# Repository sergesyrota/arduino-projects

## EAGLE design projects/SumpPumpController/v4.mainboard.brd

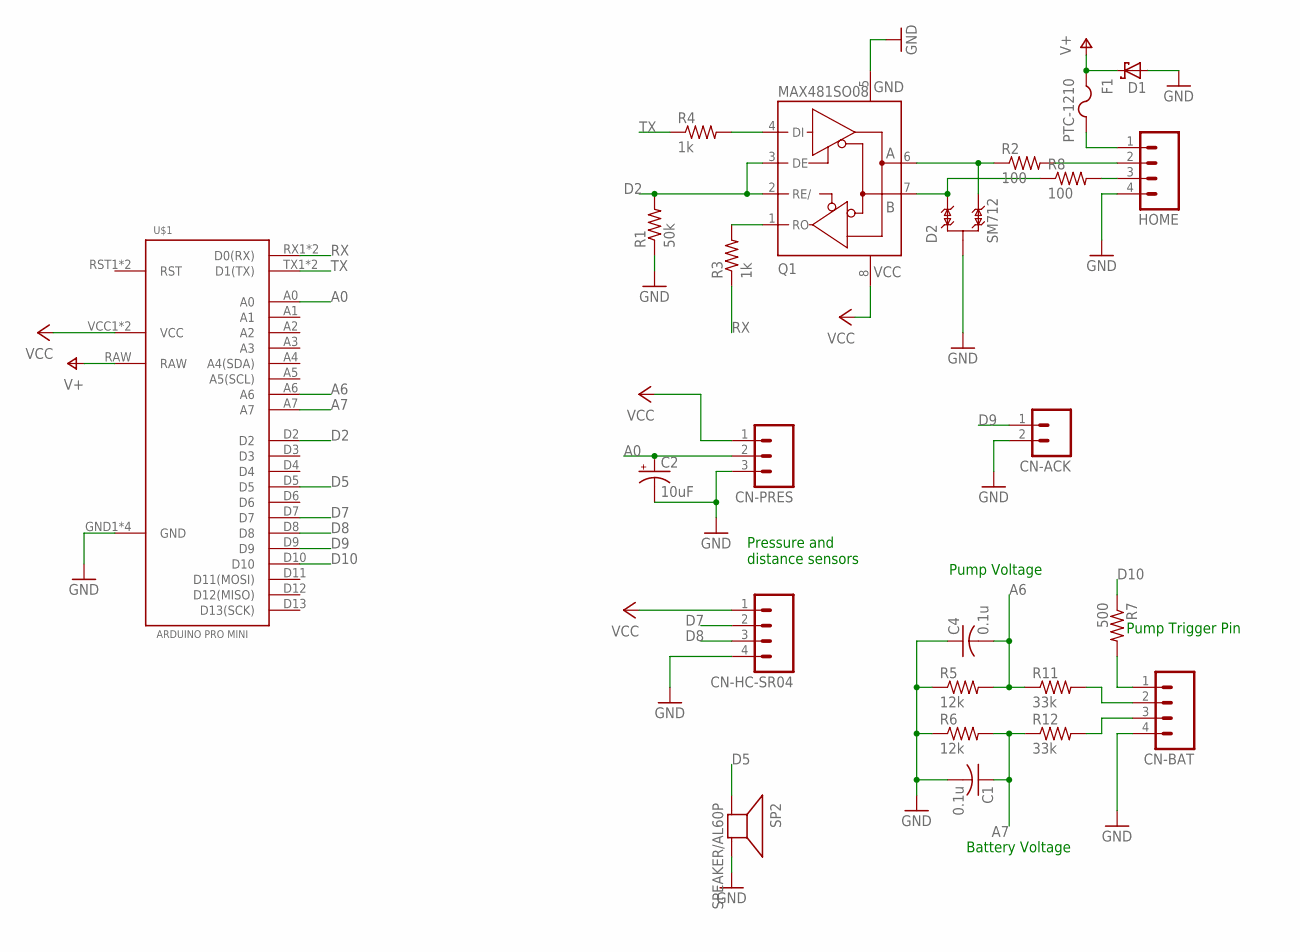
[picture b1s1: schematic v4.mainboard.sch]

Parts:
C1, C4: 0.1u; C0603K
C2: 10uF; E2-5
CN-ACK: M02; 02P
CN-BAT: M04; 04P
CN-HC-SR04: M04; 04P
CN-PRES: M03; 03P
D1: SCHOTTKY-DIODESMC; SMC
D2: SM712; SOT23-3
F1: PTC-1210; 1210
HOME: M04; 04P
Q1: MAX481SO08; SO08
R1: 50k; R0603
R2, R8: 100; R0603
R3, R4: 1k; R0603
R5, R6: 12k; R0603
R7: 500; R0603
R11, R12: 33k; R0603
SP2: SPEAKER/AL60P; AL60P
U$1: ARDUINO-PRO-MINI

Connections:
A0: C2.+, CN-PRES.2, U$1.A0
A6: C4.2, R5.2, R11.1, U$1.A6
A7: C1.1, R6.2, R12.1, U$1.A7
D2: Q1.2 (RE/), Q1.3 (DE), R1.2, U$1.D2
D5: SP2.1 (+), U$1.D5
D7: CN-HC-SR04.2, U$1.D7
D8: CN-HC-SR04.3, U$1.D8
D9: CN-ACK.1, U$1.D9
D10: R7.1, U$1.D10
GND: C1.2, C2.-, C4.1, CN-ACK.2, CN-BAT.4, CN-HC-SR04.4, CN-PRES.3, D1.A, D2.3, HOME.4, Q1.5 (GND), R1.1, R5.1, R6.1, SP2.2 (-), U$1.GND1 (GND), U$1.GND2 (GND), U$1.GND3 (GND), U$1.GND4 (GND)
unnamed: F1.2, HOME.1
unnamed: D2.2, Q1.7 (B), R8.1
unnamed: Q1.1 (RO), R3.2
unnamed: Q1.4 (DI), R4.2
unnamed: HOME.3, R8.2
unnamed: HOME.2, R2.2
unnamed: D2.1, Q1.6 (A), R2.1
unnamed: CN-BAT.2, R11.2
unnamed: CN-BAT.3, R12.2
unnamed: CN-BAT.1, R7.2
RX: R3.1, U$1.RX1 (D0(RX)), U$1.RX2 (D0(RX))
TX: R4.1, U$1.TX1 (D1(TX)), U$1.TX2 (D1(TX))
V+: D1.C, F1.1, U$1.RAW
VCC: CN-HC-SR04.1, CN-PRES.1, Q1.8 (+5V), U$1.VCC1 (VCC), U$1.VCC2 (VCC)

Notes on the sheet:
Battery Voltage
Pump Voltage
Pump Trigger Pin
Pressure and distance sensors

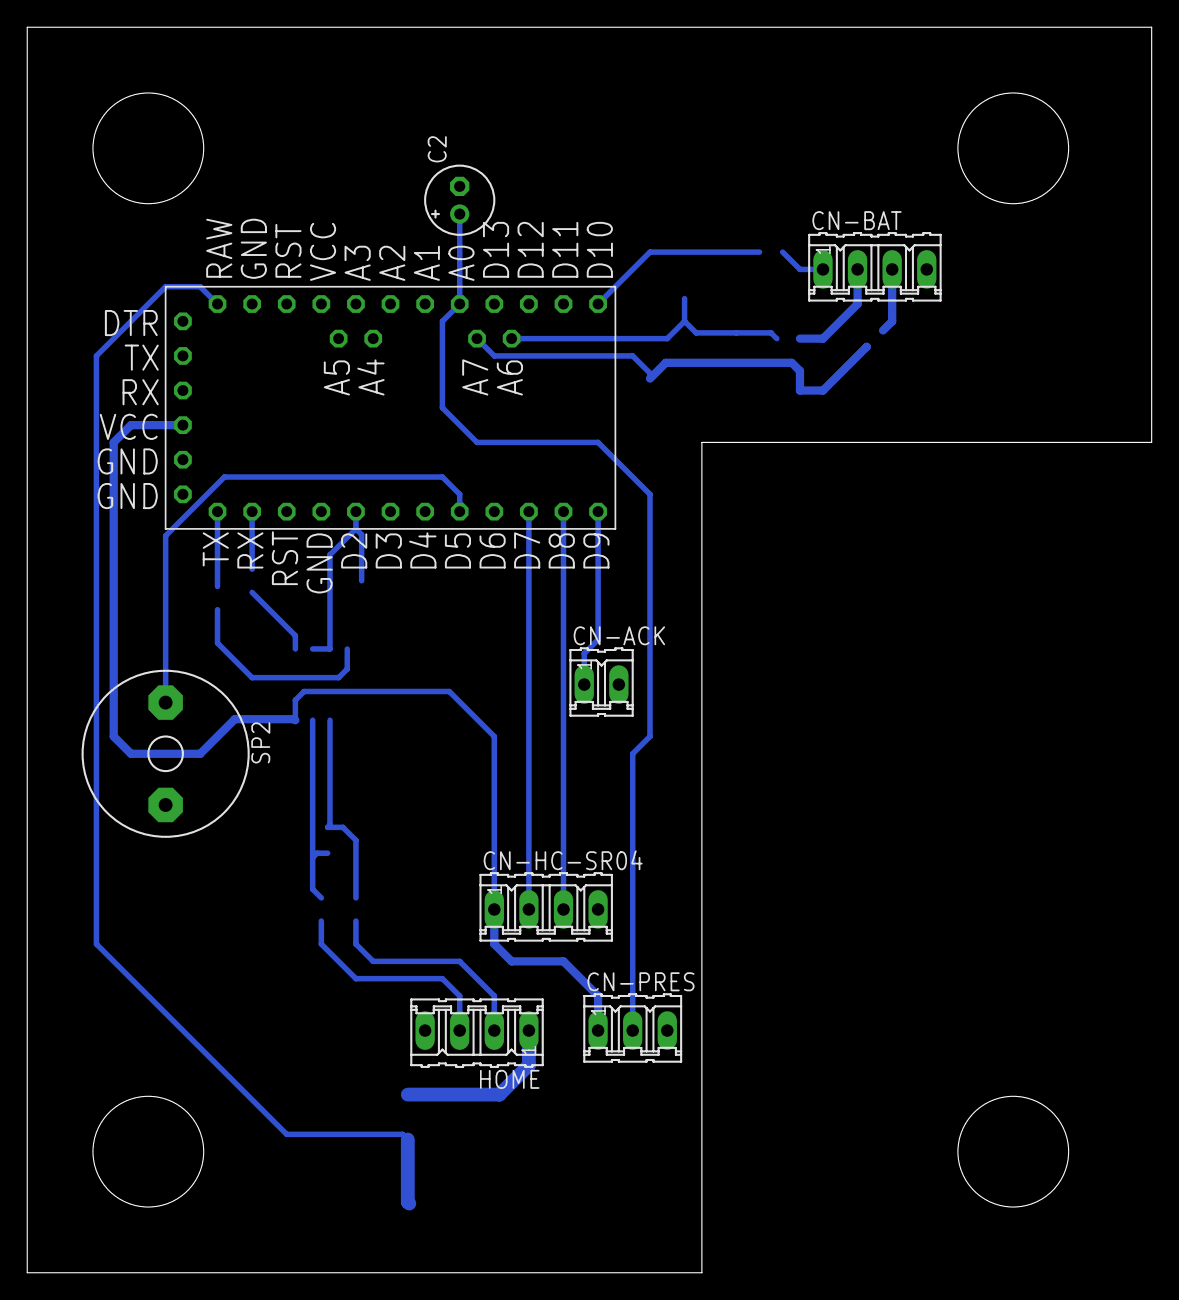
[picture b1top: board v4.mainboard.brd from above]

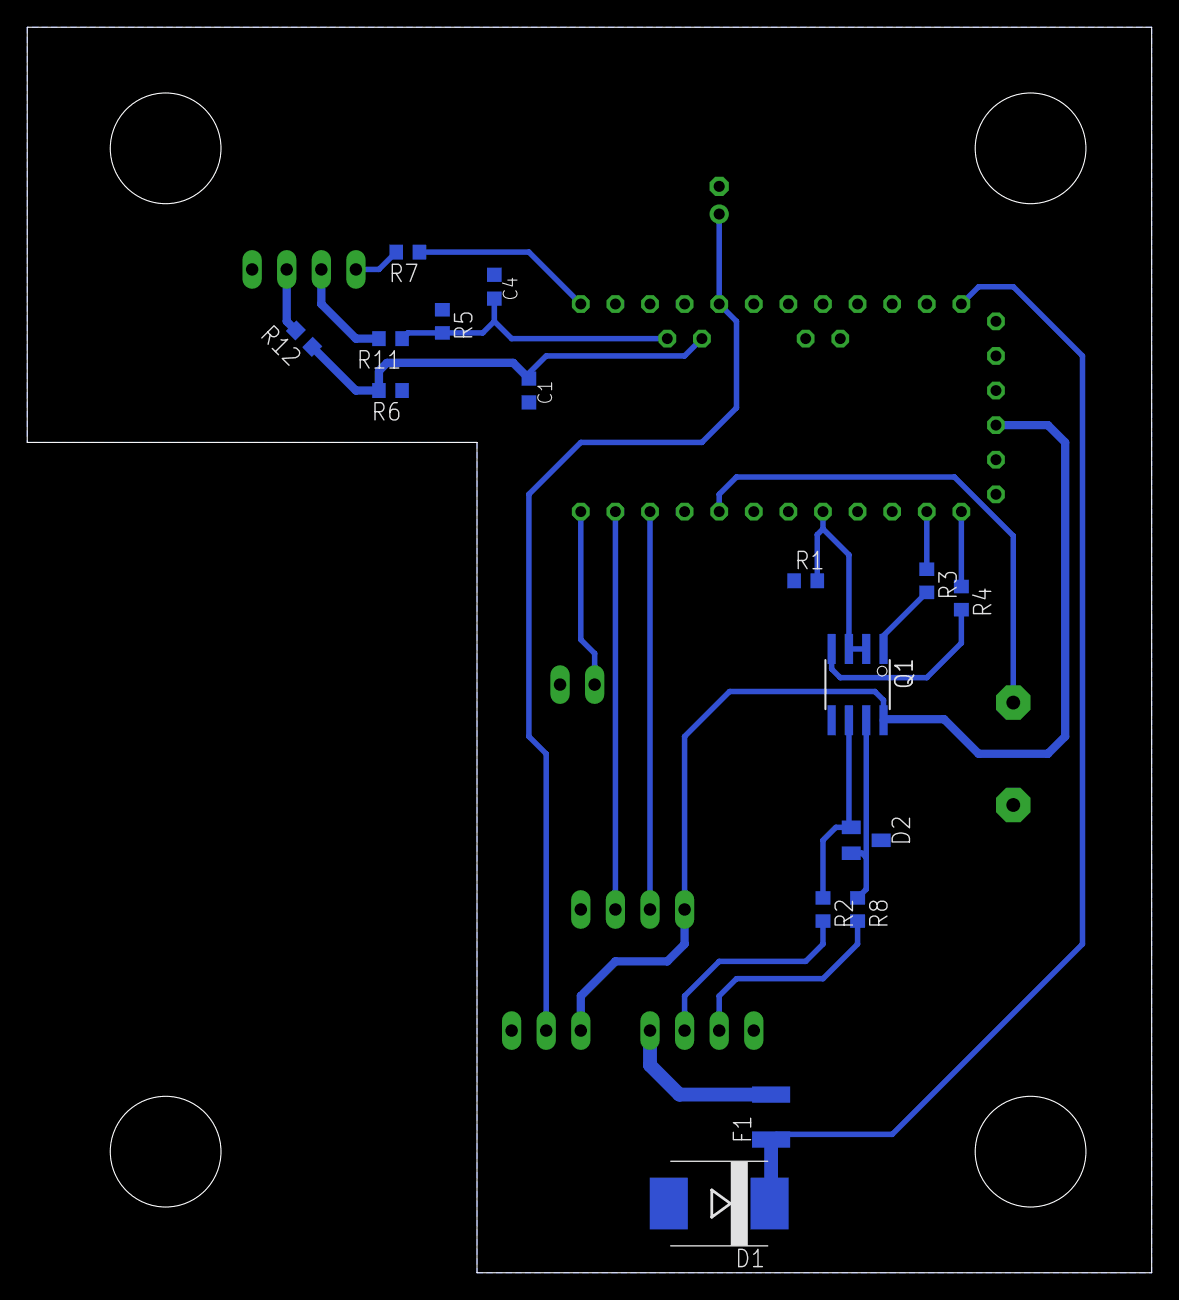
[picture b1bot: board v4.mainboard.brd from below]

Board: 2 copper layers, 82.5 x 91.4 mm, 24 parts (16 on the bottom side), 24 nets.

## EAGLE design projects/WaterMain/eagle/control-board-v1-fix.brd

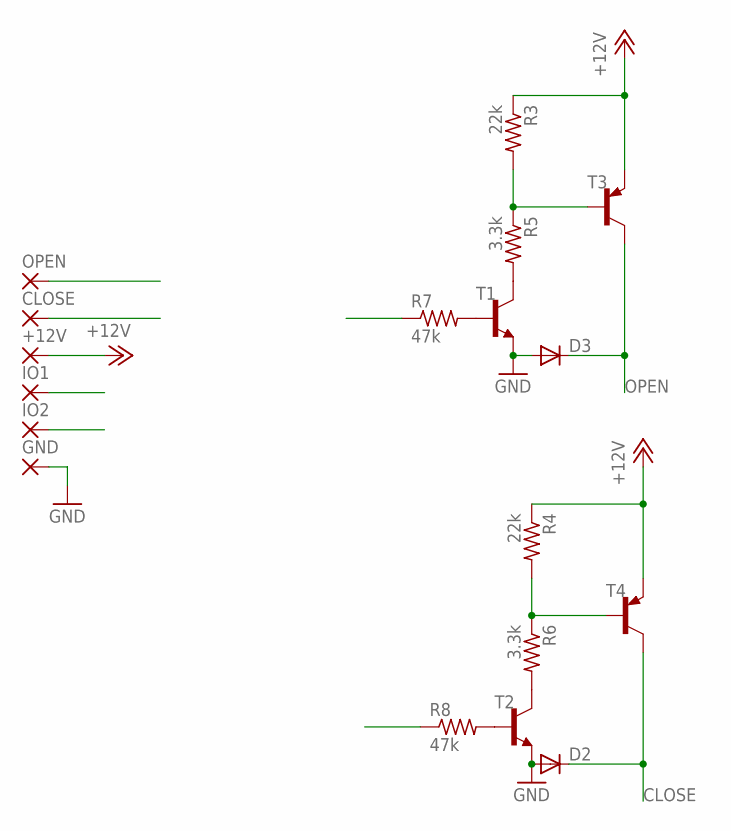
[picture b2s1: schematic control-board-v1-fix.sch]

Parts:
+12V: 1,6/0,8
CLOSE: 1,6/0,8
D2, D3: DIODE-MICROMELF-W; MICROMELF-W
GND: 1,6/0,8
IO1, IO2: 1,6/0,8
OPEN: 1,6/0,8
R3, R4: 22k; R0603
R5, R6: 3.3k; R0603
R7, R8: 47k; R0603
T1, T2: BC808-NPN-SOT23-BEC; SOT23-BEC
T3, T4: BC807-16-PNP-SOT23-BEC; SOT23-BEC

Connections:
+12V: +12V.1, R3.1, R4.1, T3.E, T4.E
CLOSE: CLOSE.1, D2.C, T4.C
GND: D2.A, D3.A, GND.1, T1.E, T2.E
IO1: IO1.1, R7.1
IO2: IO2.1, R8.1
unnamed: R4.2, R6.1, T4.B
unnamed: R3.2, R5.1, T3.B
unnamed: R7.2, T1.B
unnamed: R8.2, T2.B
unnamed: R5.2, T1.C
unnamed: R6.2, T2.C
OPEN: D3.C, OPEN.1, T3.C

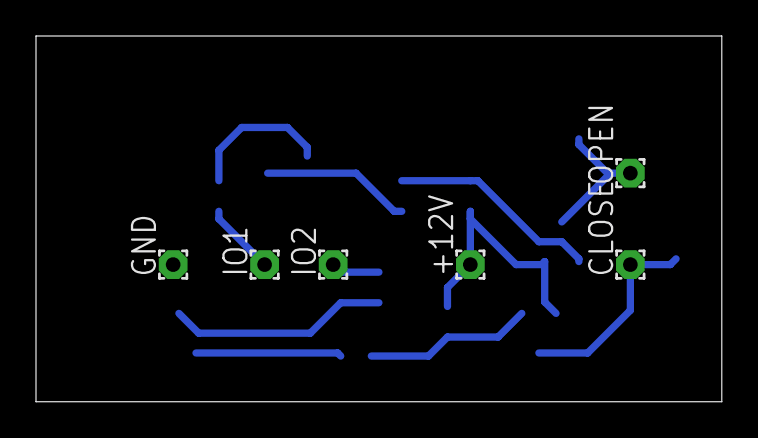
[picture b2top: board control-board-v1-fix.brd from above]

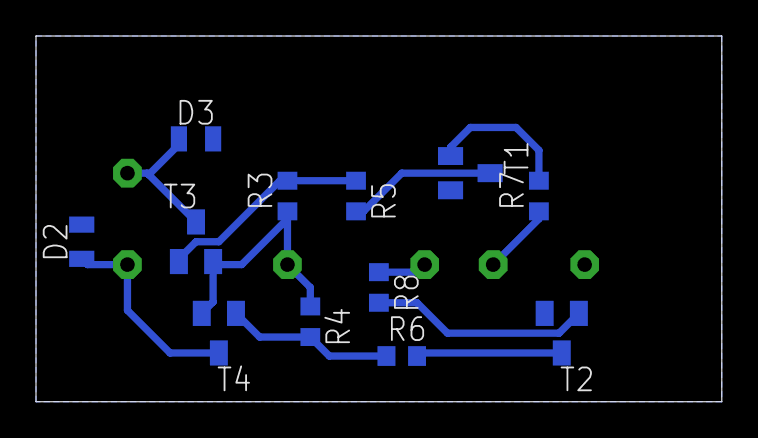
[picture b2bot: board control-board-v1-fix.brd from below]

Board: 2 copper layers, 38.1 x 20.3 mm, 18 parts (12 on the bottom side), 12 nets.

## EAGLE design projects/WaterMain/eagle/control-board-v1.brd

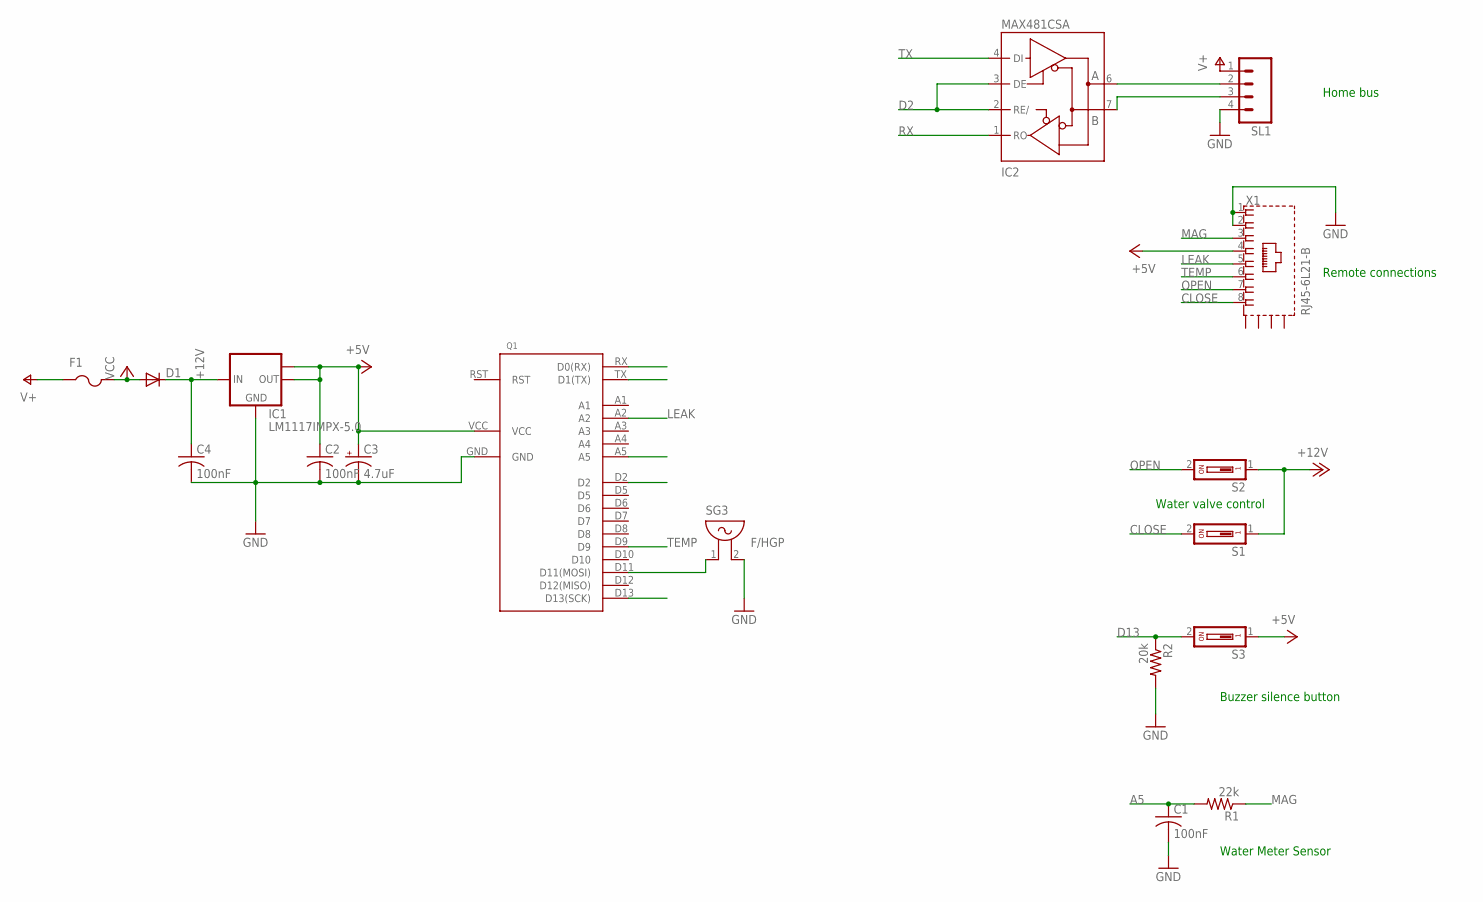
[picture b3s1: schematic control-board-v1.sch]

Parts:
C1, C2, C4: 100nF; C0603K
C3: 4.7uF; E1,8-4
D1: DIODE-MICROMELF-W; MICROMELF-W
F1: PTCFUSE-1812; 1812
IC1: LM1117IMPX-5.0; SOT223
IC2: MAX481CSA; SO08
Q1: HOME-CPU-V1
R1: 22k; R0603
R2: 20k; R0603
S1, S2, S3: DS01; DS-01
SG3: F/HGP
SL1: M04; 04P
X1: RJ45-6L21-B; RJ45-SHIELD1

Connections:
+12V: C4.1, D1.C, IC1.3 (IN), S1.1, S2.1
A5: C1.1, Q1.A5, R1.2
CLOSE: S1.2, X1.8
D2: IC2.2 (RE/), IC2.3 (DE), Q1.D2
D13: Q1.D13 (D13(SCK)), R2.1, S3.2
GND: C1.2, C2.2, C3.-, C4.2, IC1.1 (GND), IC2.5 (GND), Q1.GND, R2.2, SG3.2, SL1.4, X1.1, X1.2
LEAK: Q1.A2, X1.5
MAG: R1.1, X1.3
unnamed: D1.A, F1.2
unnamed: Q1.D11 (D11(MOSI)), SG3.1
unnamed: IC2.6 (A), SL1.2
unnamed: IC2.7 (B), SL1.3
OPEN: S2.2, X1.7
RX: IC2.1 (RO), Q1.RX (D0(RX))
TEMP: Q1.D9, X1.6
TX: IC2.4 (DI), Q1.TX (D1(TX))
V+: F1.1, SL1.1
VCC: C2.1, C3.+, IC1.2 (OUT), IC1.TAB (OUT1), IC2.8 (VCC), Q1.VCC, S3.1, X1.4

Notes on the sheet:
Water Meter Sensor
Buzzer silence button
Water valve control
Remote connections
Home bus

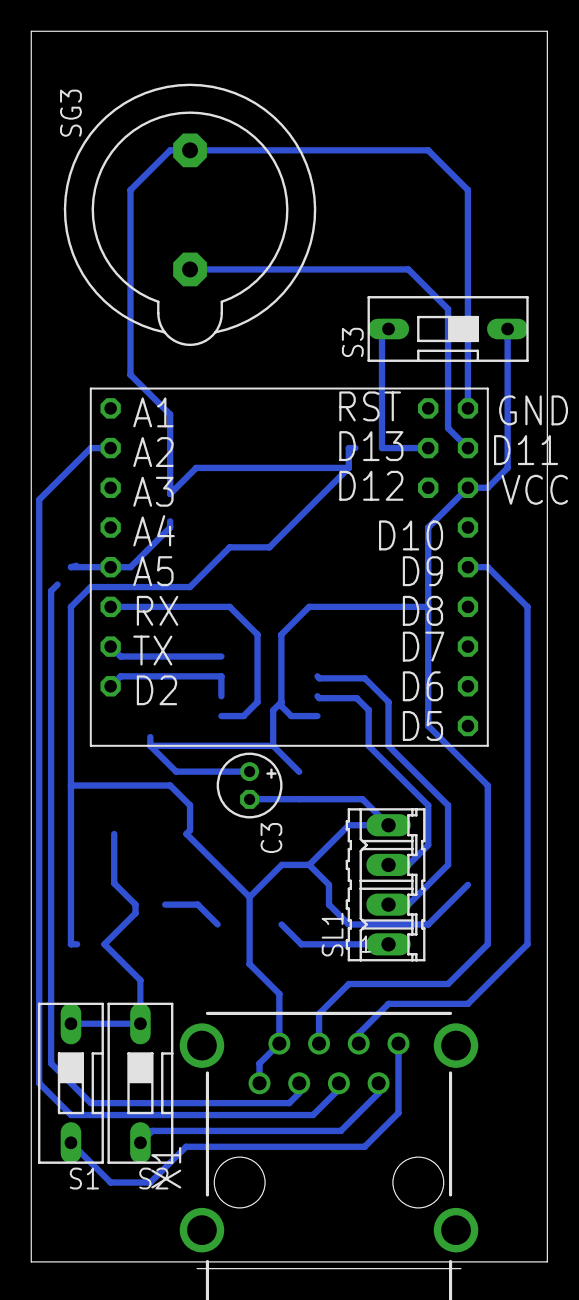
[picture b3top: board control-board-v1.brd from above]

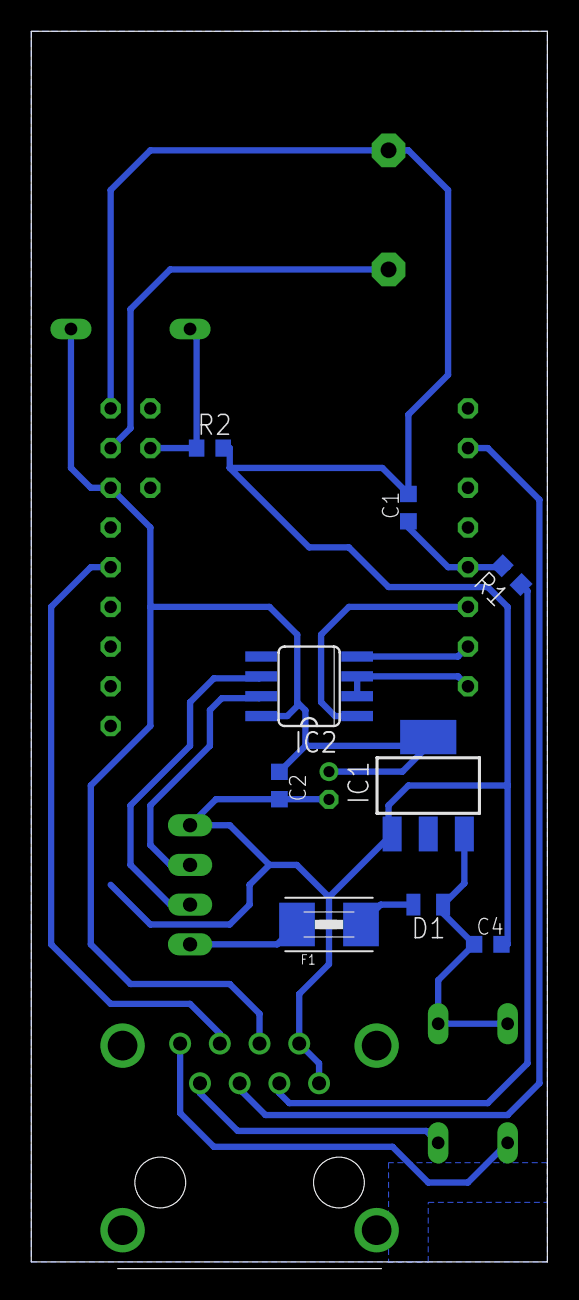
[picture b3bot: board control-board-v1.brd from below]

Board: 2 copper layers, 33.0 x 78.7 mm, 17 parts (9 on the bottom side), 18 nets.

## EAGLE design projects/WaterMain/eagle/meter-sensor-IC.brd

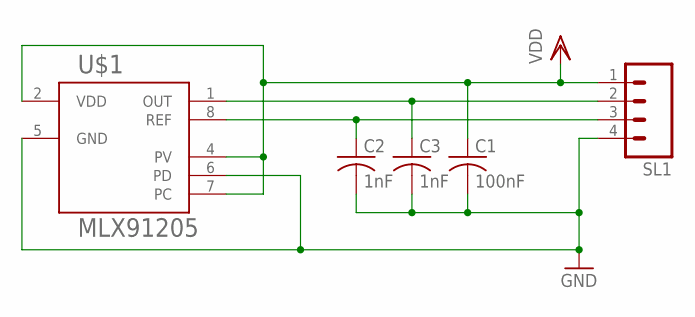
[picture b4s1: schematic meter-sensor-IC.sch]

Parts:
C1: 100nF; C050-024X044
C2, C3: 1nF; C025-024X044
SL1: M04; 04P
U$1: MLX91205; SO08

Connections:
GND: C1.2, C2.2, C3.2, SL1.4, U$1.5 (GND), U$1.6 (PD)
unnamed: C3.1, SL1.2, U$1.1 (OUT)
unnamed: C2.1, SL1.3, U$1.8 (REF)
VDD: C1.1, SL1.1, U$1.2 (VDD), U$1.4 (PV), U$1.7 (PC)

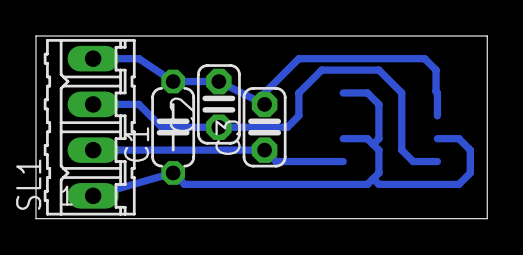
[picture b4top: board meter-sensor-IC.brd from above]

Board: 2 copper layers, 25.1 x 10.2 mm, 5 parts (1 on the bottom side), 4 nets.

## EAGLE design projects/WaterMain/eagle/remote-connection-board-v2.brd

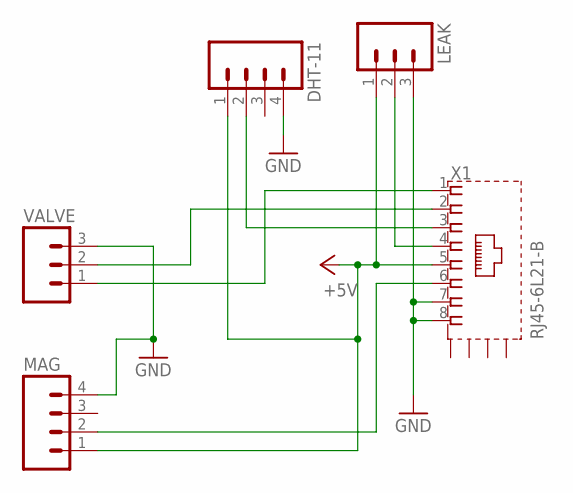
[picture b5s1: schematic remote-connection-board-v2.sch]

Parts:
DHT-11: M04; 04P
LEAK: M03; 03P
MAG: M04; 04P
VALVE: M03; 03P
X1: RJ45-6L21-B; RJ45-SHIELD1

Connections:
+5V: DHT-11.1, LEAK.1, MAG.1, X1.5
GND: DHT-11.4, LEAK.3, MAG.4, VALVE.3, X1.7, X1.8
unnamed: VALVE.2, X1.2
unnamed: VALVE.1, X1.1
unnamed: MAG.2, X1.6
unnamed: DHT-11.2, X1.3
unnamed: LEAK.2, X1.4

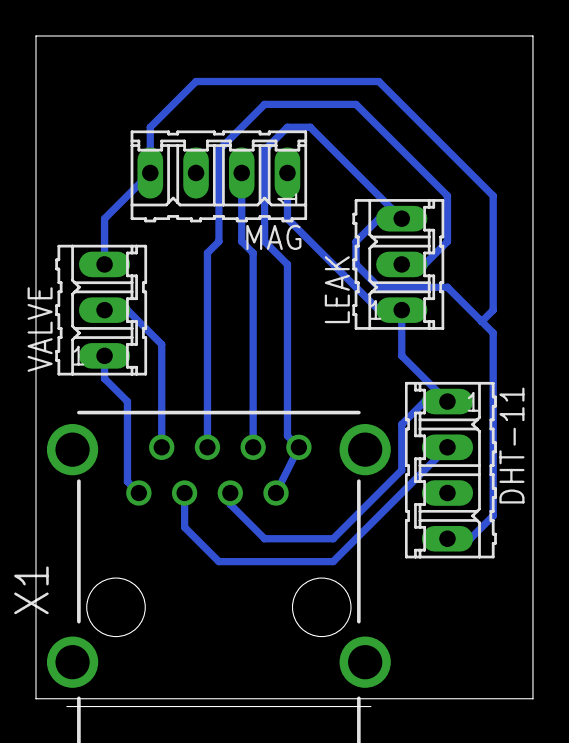
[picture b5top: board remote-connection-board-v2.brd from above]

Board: 2 copper layers, 27.6 x 36.8 mm, 5 parts (0 on the bottom side), 7 nets.

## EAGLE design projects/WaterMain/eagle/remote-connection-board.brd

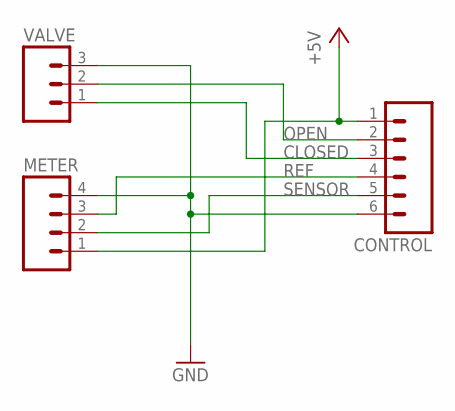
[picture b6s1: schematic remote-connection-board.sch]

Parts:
CONTROL: M06; 06P
METER: M04; 04P
VALVE: M03; 03P

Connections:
+5V: CONTROL.1, METER.1
CLOSED: CONTROL.3, VALVE.1
GND: CONTROL.6, METER.4, VALVE.3
OPEN: CONTROL.2, VALVE.2
REF: CONTROL.4, METER.3
SENSOR: CONTROL.5, METER.2

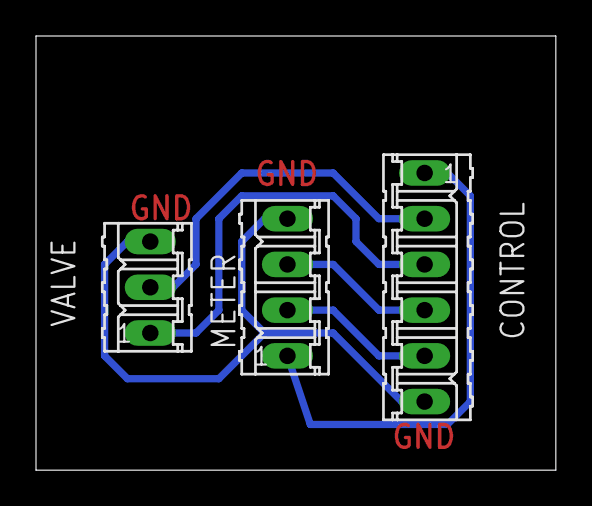
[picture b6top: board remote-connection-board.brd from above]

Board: 2 copper layers, 28.9 x 24.1 mm, 3 parts (0 on the bottom side), 6 nets.

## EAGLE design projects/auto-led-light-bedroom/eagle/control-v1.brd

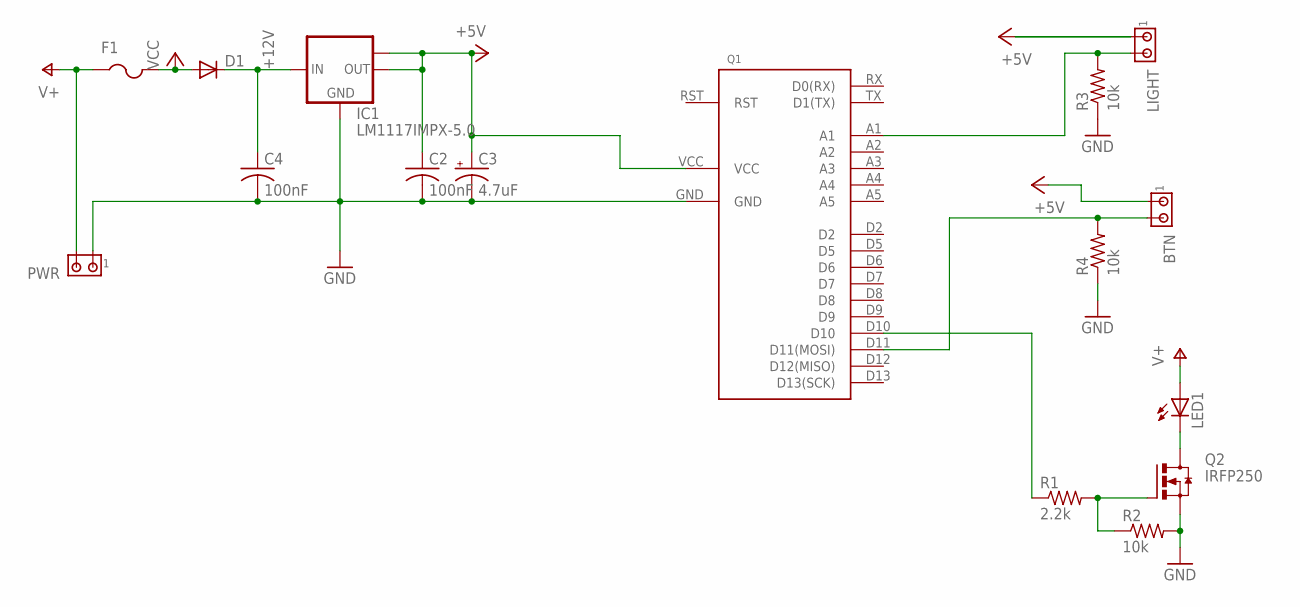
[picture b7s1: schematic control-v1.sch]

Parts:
BTN: MTA02-100; 10X02MTA
C2, C4: 100nF; C0603K
C3: 4.7uF; E1,8-4
D1: DIODE-MICROMELF-W; MICROMELF-W
F1: PTCFUSE-1812; 1812
IC1: LM1117IMPX-5.0; SOT223
LED1: LED3MM
LIGHT: MTA02-100; 10X02MTA
PWR: MTA02-100; 10X02MTA
Q1: HOME-CPU-V1
Q2: IRFP250; TO-247AD-V
R1: 2.2k; R0603
R2, R3, R4: 10k; R0603

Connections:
+12V: C4.1, D1.C, IC1.3 (IN)
GND: C2.2, C3.-, C4.2, IC1.1 (GND), PWR.1, Q1.GND, Q2.S, R2.2, R3.1, R4.1
unnamed: D1.A, F1.2
unnamed: LED1.K (C), Q2.D
unnamed: Q1.D10, R1.1
unnamed: Q2.G, R1.2, R2.1
unnamed: LIGHT.2, Q1.A1, R3.2
unnamed: BTN.2, Q1.D11 (D11(MOSI)), R4.2
V+: F1.1, LED1.A, PWR.2
VCC: BTN.1, C2.1, C3.+, IC1.2 (OUT), IC1.TAB (OUT1), LIGHT.1, Q1.VCC

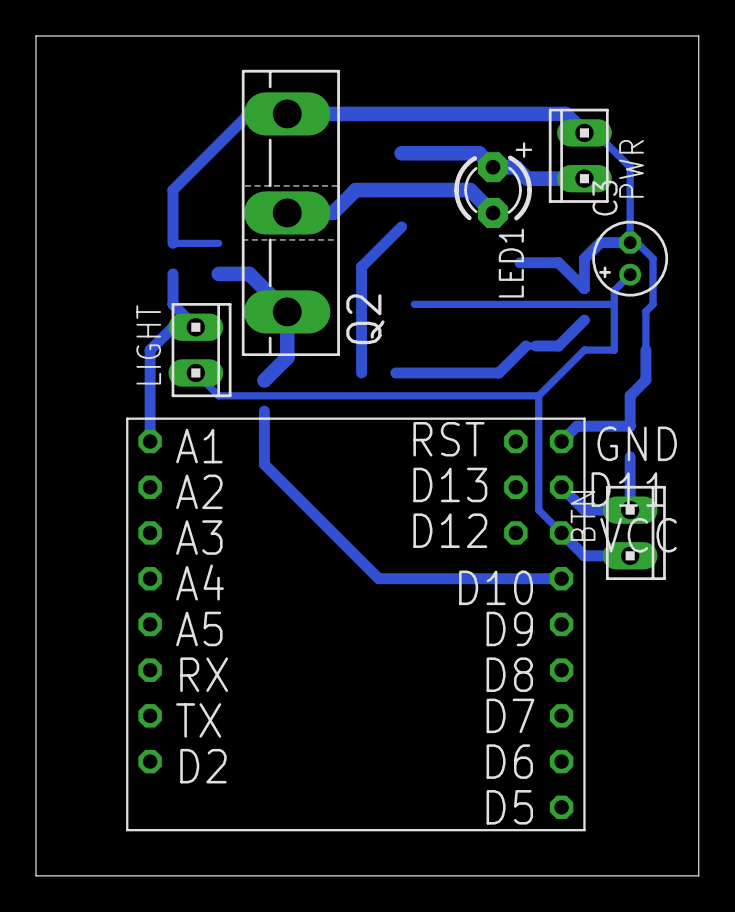
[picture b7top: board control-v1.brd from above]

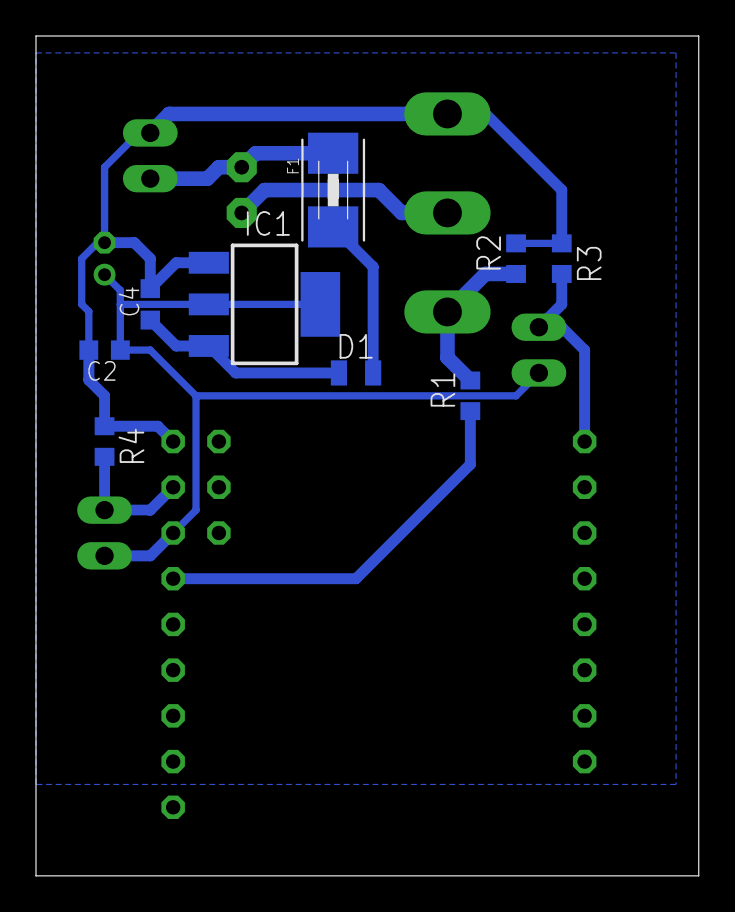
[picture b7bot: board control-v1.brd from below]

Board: 2 copper layers, 36.8 x 46.7 mm, 16 parts (9 on the bottom side), 10 nets.
